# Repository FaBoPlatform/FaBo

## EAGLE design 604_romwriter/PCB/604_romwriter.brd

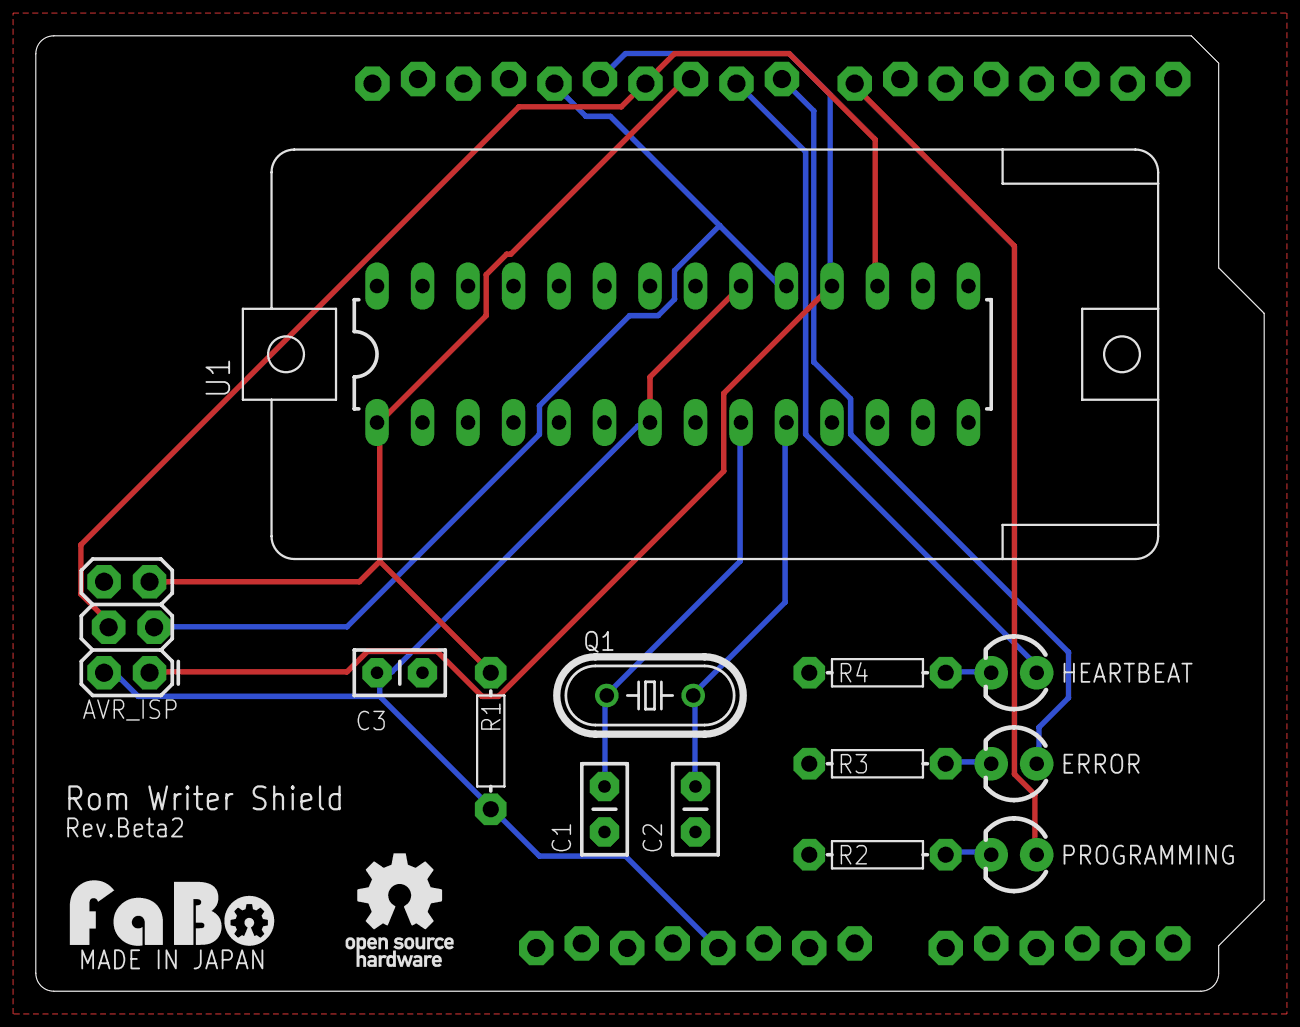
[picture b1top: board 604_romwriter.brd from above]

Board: 2 copper layers, 68.6 x 53.3 mm, 16 parts (0 on the bottom side), 14 nets.

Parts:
C1, C2: 22pF; CAP-PTH-SMALL
C3: 0.01pF; CAP-PTH-SMALL
ERROR: LED3MM
HEARTBEAT: LED3MM
JP1: AVR_ISP; 2X3_LOCK
PROGRAMMING: LED3MM
Q1: HC49/S
R1: 10k; RES-AXL-REGULAR
R2, R3, R4: 1k; RES-AXL-REGULAR
U1: ZERO_PRESSURE_SOCKET; ZERO_PRESSURE_SOCKET_DIL28
U2: ARDUINO_UNO_R3_NOLABEL
U$1: LOGO_FABO_M
U$3: LOGO_OSHW_T_M

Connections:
+5V: C3.1, JP1.2, R1.P$2, U1.7, U1.20, U2.5V
ERR_LED: ERROR.A, U2.D8
GND: C1.2, C2.2, C3.2, JP1.6, R2.P$1, R3.P$1, R4.P$1, U1.8, U1.22, U2.GND1, U2.GND2, U2.GND3
HBT_LED: HEARTBEAT.A, U2.D9
MISO: JP1.1, U1.18, U2.D12
MOSI: JP1.4, U1.17, U2.D11
unnamed: PROGRAMMING.K, R2.P$2
unnamed: ERROR.K, R3.P$2
unnamed: HEARTBEAT.K, R4.P$2
PGM_LED: PROGRAMMING.A, U2.D7
RESET: JP1.5, R1.P$1, U1.1, U2.D10
SCK: JP1.3, U1.19, U2.D13
XTAL1: C1.1, Q1.1, U1.9
XTAL2: C2.1, Q1.2, U1.10

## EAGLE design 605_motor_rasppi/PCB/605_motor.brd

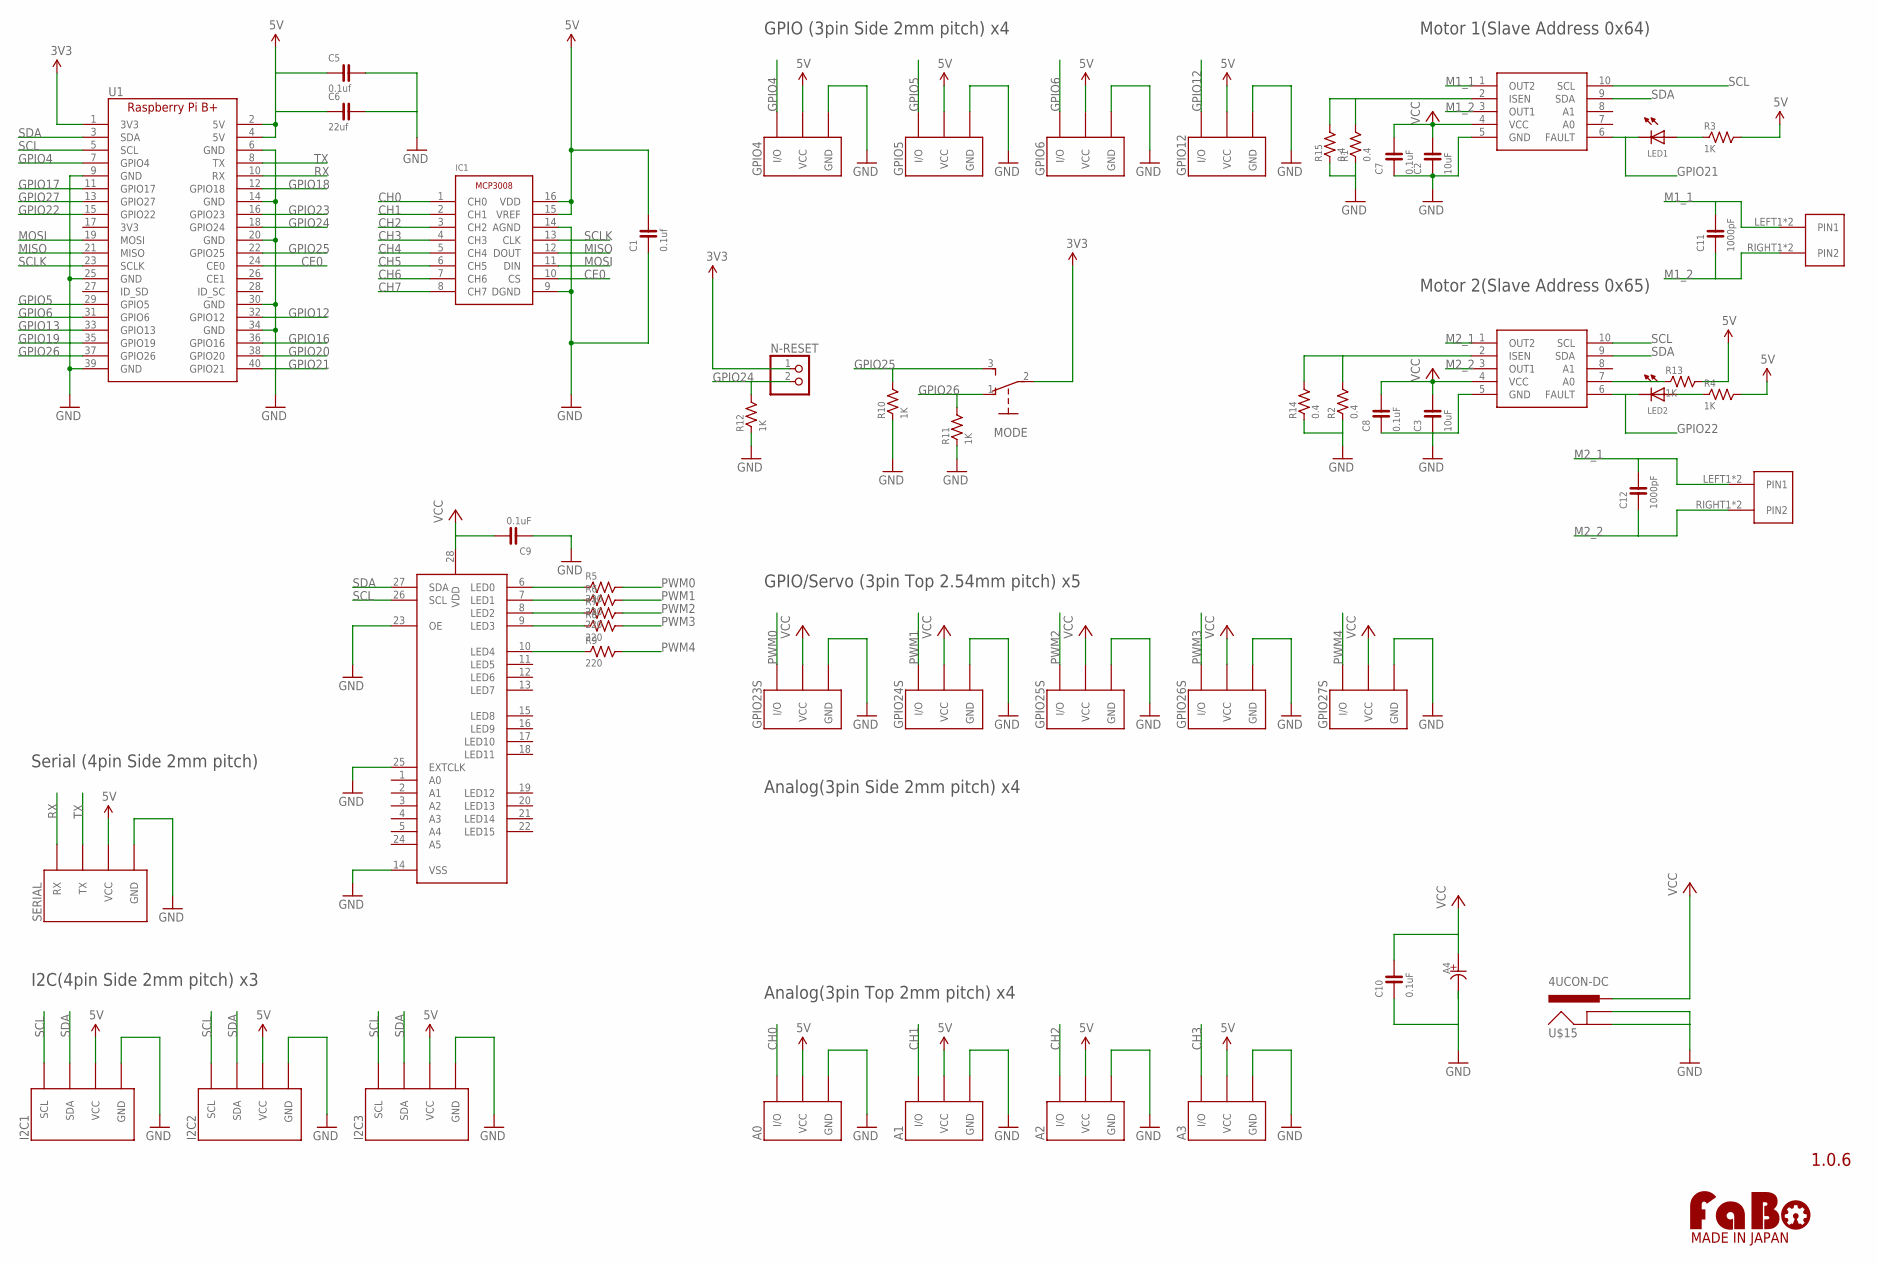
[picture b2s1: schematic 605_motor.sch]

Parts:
A0, A1, A2, A3: FABO_BRICK_3PIN-B03B-PASK-1; FABO_BRICK_3PIN_B03B-PASK-1
A4: CAPACITOR-ALUMIN; H13
C1, C5: 0.1uf; 0603
C2, C3: 10uF; 0603
C6: 22uf; 0603
C7, C8, C9, C10: 0.1uF; 0603
C11, C12: 1000pF; 0603
GPIO4, GPIO5, GPIO6, GPIO12: FABO_BRICK_3PIN-S03B-PASK-2; FABO_BRICK_3PIN_S03B-PASK-2
GPIO23S, GPIO24S, GPIO25S, GPIO26S, GPIO27S: FABO_BRICK_3PIN-HEADER; FABO_BRICK_3PIN_HEADER
I2C1, I2C2, I2C3: FABO_BRICK_I2C-S04B-PASK-2; FABO_BRICK_I2C_S04B-PASK-2
IC1: MICROCHIP-MCP3008
LED1, LED2: LED-0603; 0603
MODE: SLIDE; EG1218
N-RESET: PINHD-1X2; 1X02
R1, R2, R14, R15: 0.4; 0603
R3, R4, R10, R11, R12, R13: 1K; 0603
R5, R6, R7, R8, R9: 220; 0603
SERIAL: FABO_BRICK_SERIAL-S04B-PASK-2; FABO_BRICK_SERIAL_S04B-PASK-2
U1: RASPBERRY_PI_B+
U$8, U$10: DRV8830
U$9: PCA9685
U$12, U$13: ML-1400-S1
U$14: LOGO_FABO-M; LOGO_FABO_MS
U$15: 4UCON-DC

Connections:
3V3: MODE.2, N-RESET.1, U1.1 (3V3)
5V: A0.VCC, A1.VCC, A2.VCC, A3.VCC, C1.2, C5.1, C6.1, GPIO4.VCC, GPIO5.VCC, GPIO6.VCC, GPIO12.VCC, I2C1.VCC, I2C2.VCC, I2C3.VCC, IC1.15 (VREF), IC1.16 (VDD), R3.2, R4.2, R13.2, SERIAL.VCC, U1.2 (5V), U1.4 (5V)
CE0: IC1.10 (CS), U1.24 (CE0)
CH0: A0.I/O, IC1.1 (CH0)
CH1: A1.I/O, IC1.2 (CH1)
CH2: A2.I/O, IC1.3 (CH2)
CH3: A3.I/O, IC1.4 (CH3)
CH4: IC1.5 (CH4)
CH5: IC1.6 (CH5)
CH6: IC1.7 (CH6)
CH7: IC1.8 (CH7)
GND: A0.GND, A1.GND, A2.GND, A3.GND, A4.MINUS (-), C1.1, C2.1, C3.1, C5.2, C6.2, C7.1, C8.1, C9.1, C10.1, GPIO4.GND, GPIO5.GND, GPIO6.GND, GPIO12.GND, GPIO23S.GND, GPIO24S.GND, GPIO25S.GND, GPIO26S.GND, GPIO27S.GND, I2C1.GND, I2C2.GND, I2C3.GND, IC1.9 (DGND), IC1.14 (AGND), R1.1, R2.1, R10.1, R11.1, R12.1, R14.1, R15.1, SERIAL.GND, U1.6 (GND), U1.9 (GND), U1.14 (GND), U1.20 (GND), U1.25 (GND), U1.30 (GND), U1.34 (GND), U1.39 (GND), U$8.5 (GND), U$9.14 (VSS), U$9.23 (OE), U$9.25 (EXTCLK), U$10.5 (GND), U$15.GND1 (GND), U$15.GND2 (GNDBREAK)
GPIO4: GPIO4.I/O, U1.7 (GPIO4)
GPIO5: GPIO5.I/O, U1.29 (GPIO5)
GPIO6: GPIO6.I/O, U1.31 (GPIO6)
GPIO12: GPIO12.I/O, U1.32 (GPIO12)
GPIO13: U1.33 (GPIO13)
GPIO16: U1.36 (GPIO16)
GPIO17: U1.11 (GPIO17)
GPIO18: U1.12 (GPIO18)
GPIO19: U1.35 (GPIO19)
GPIO20: U1.38 (GPIO20)
GPIO21: LED1.CATHODE, U1.40 (GPIO21), U$8.6 (FAULT)
GPIO22: LED2.CATHODE, U1.15 (GPIO22), U$10.6 (FAULT)
GPIO23: U1.16 (GPIO23)
GPIO24: N-RESET.2, R12.2, U1.18 (GPIO24)
GPIO25: MODE.3, R10.2, U1.22 (GPIO25)
GPIO26: MODE.1, R11.2, U1.37 (GPIO26)
GPIO27: U1.13 (GPIO27)
LED0: R5.1, U$9.6 (LED0)
LED1: R6.1, U$9.7 (LED1)
LED2: R7.1, U$9.8 (LED2)
LED3: R8.1, U$9.9 (LED3)
LED4: R9.1, U$9.10 (LED4)
M1_1: C11.2, U$8.1 (OUT2), U$12.LEFT1 (PIN1), U$12.LEFT2 (PIN1)
M1_2: C11.1, U$8.3 (OUT1), U$12.RIGHT1 (PIN2), U$12.RIGHT2 (PIN2)
M2_1: C12.2, U$10.1 (OUT2), U$13.LEFT1 (PIN1), U$13.LEFT2 (PIN1)
M2_2: C12.1, U$10.3 (OUT1), U$13.RIGHT1 (PIN2), U$13.RIGHT2 (PIN2)
MISO: IC1.12 (DOUT), U1.21 (MISO)
MOSI: IC1.11 (DIN), U1.19 (MOSI)
unnamed: R1.2, R15.2, U$8.2 (ISEN)
unnamed: R2.2, R14.2, U$10.2 (ISEN)
unnamed: LED1.ANODE, R3.1
unnamed: R13.1, U$10.7 (A0)
unnamed: LED2.ANODE, R4.1
PWM0: GPIO23S.I/O, R5.2
PWM1: GPIO24S.I/O, R6.2
PWM2: GPIO25S.I/O, R7.2
PWM3: GPIO26S.I/O, R8.2
PWM4: GPIO27S.I/O, R9.2
RX: SERIAL.RX, U1.10 (RX)
SCL: I2C1.SCL, I2C2.SCL, I2C3.SCL, U1.5 (SCL), U$8.10 (SCL), U$9.26 (SCL), U$10.10 (SCL)
SCLK: IC1.13 (CLK), U1.23 (SCLK)
SDA: I2C1.SDA, I2C2.SDA, I2C3.SDA, U1.3 (SDA), U$8.9 (SDA), U$9.27 (SDA), U$10.9 (SDA)
TX: SERIAL.TX, U1.8 (TX)
VCC: A4.PLUS (+), C2.2, C3.2, C7.2, C8.2, C9.2, C10.2, GPIO23S.VCC, GPIO24S.VCC, GPIO25S.VCC, GPIO26S.VCC, GPIO27S.VCC, U$8.4 (VCC), U$9.28 (VDD), U$10.4 (VCC), U$15.VCC (PWR)

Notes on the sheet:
1.0.6
GPIO (3pin Side 2mm pitch) x4
I2C(4pin Side 2mm pitch) x3
Analog(3pin Side 2mm pitch) x4
Serial (4pin Side 2mm pitch)
GPIO/Servo (3pin Top 2.54mm pitch) x5
Analog(3pin Top 2mm pitch) x4
Motor 1(Slave Address 0x64)
Motor 2(Slave Address 0x65)

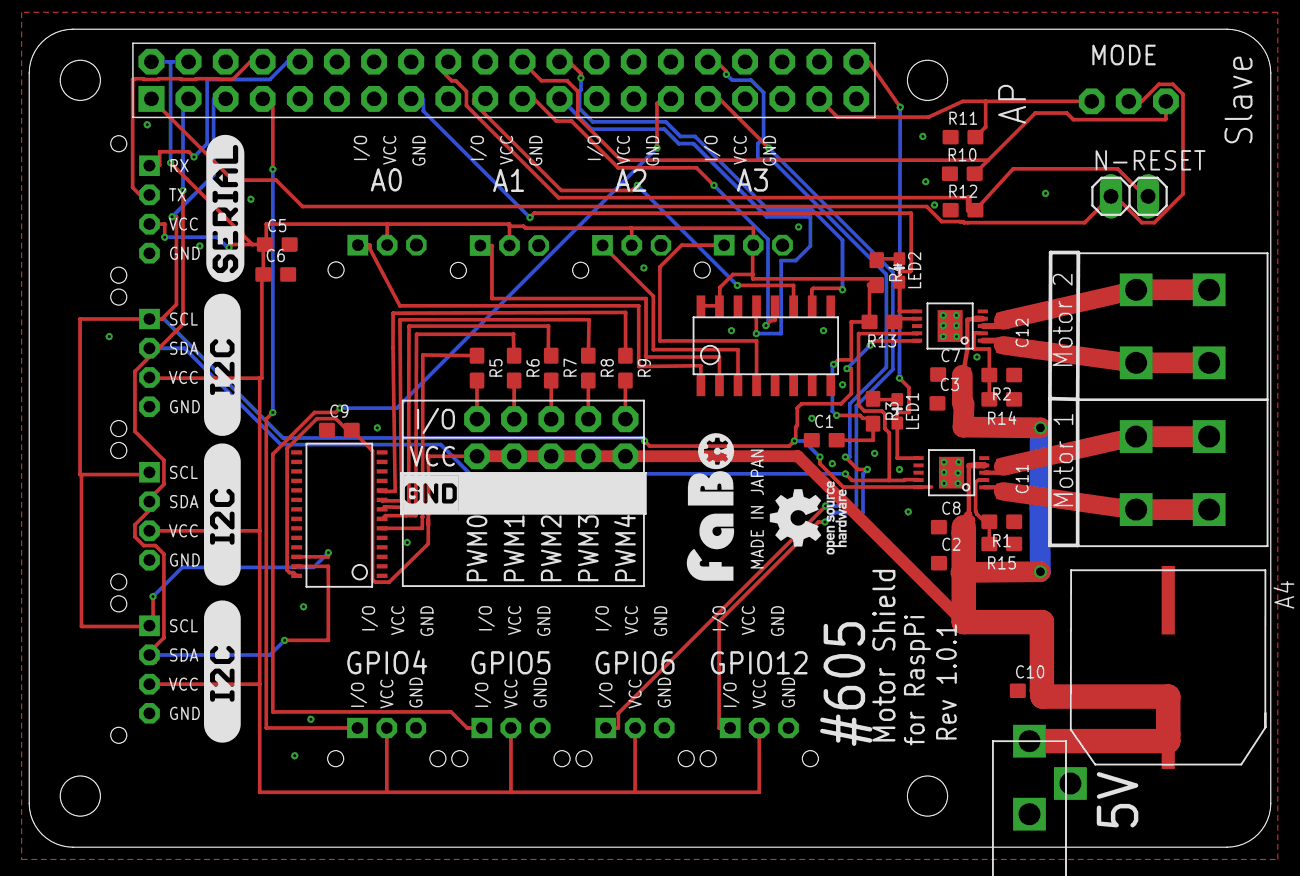
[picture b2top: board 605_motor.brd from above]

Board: 2 copper layers, 85.0 x 56.0 mm, 63 parts (0 on the bottom side), 44 nets.

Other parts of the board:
U$2, U$5, U$6: LOGO_SILK_I2C
U$3: LOGO_SILK_SERIAL2
U$4: LOGO_OSHW_T_MS
U$7: LOGO_SILK_GND

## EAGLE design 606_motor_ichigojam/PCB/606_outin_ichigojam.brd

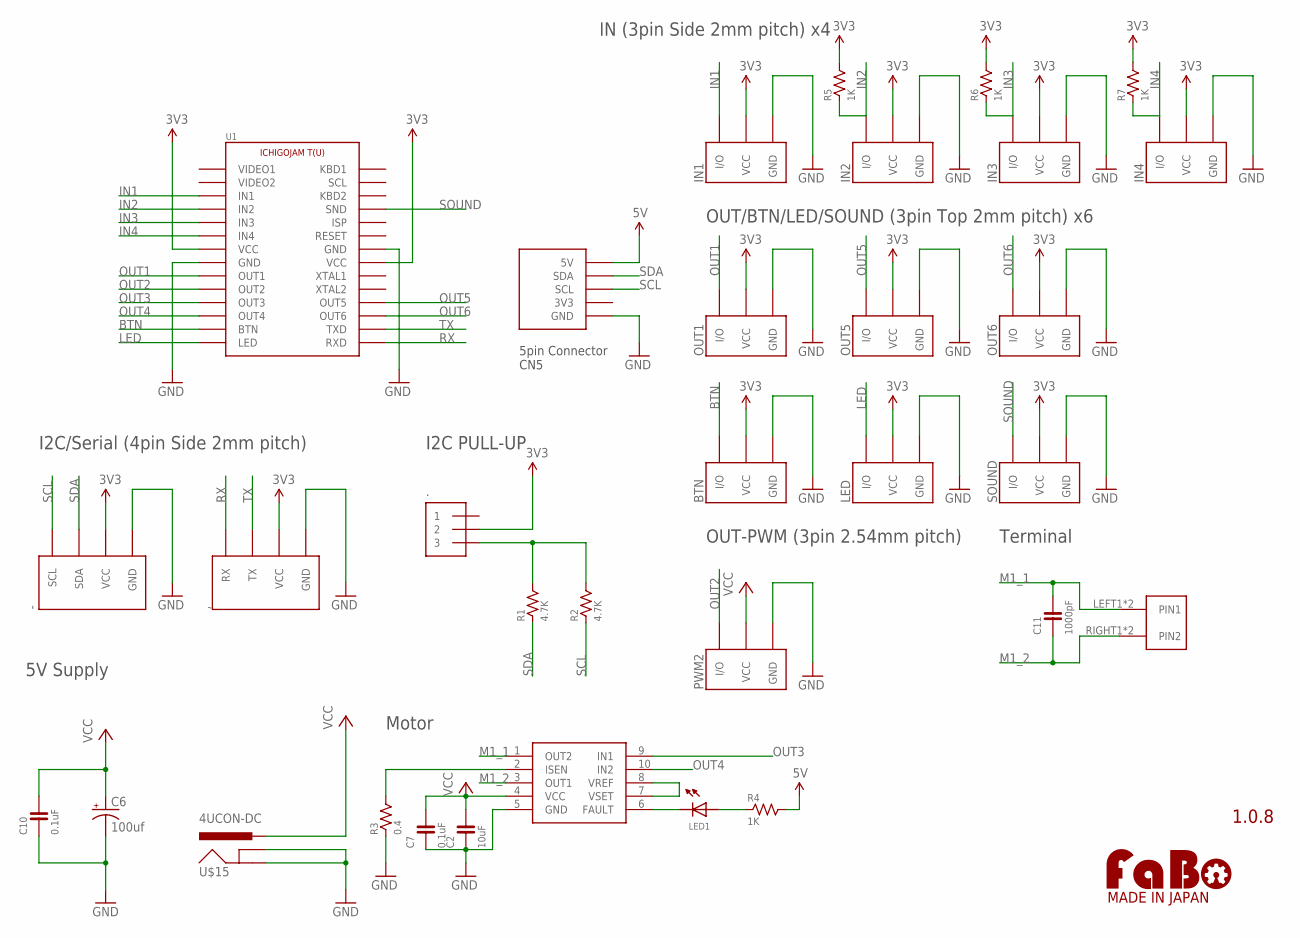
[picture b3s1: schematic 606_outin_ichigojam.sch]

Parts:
,: FABO_BRICK_SERIAL-S04B-PASK-2_LONG; FABO_BRICK_SERIAL_S04B-PASK-2_LONG
-: FABO_BRICK_I2C-S04B-PASK-2_LONG; FABO_BRICK_I2C_S04B-PASK-2_LONG
.: PIN_HEADER_1X3; PIN_1X3
BTN: FABO_BRICK_3PIN-B03B-PASK-1; FABO_BRICK_3PIN_B03B-PASK-1
C2: 10uF; 0603
C6: 100uf; 153CLV-0405
C7, C10: 0.1uF; 0603
C11: 1000pF; 0603
IN1, IN2, IN3, IN4: FABO_BRICK_3PIN-B03B-PASK-1; FABO_BRICK_3PIN_B03B-PASK-1
LED: FABO_BRICK_3PIN-B03B-PASK-1; FABO_BRICK_3PIN_B03B-PASK-1
LED1: LED-0603; 0603
OUT1, OUT5, OUT6: FABO_BRICK_3PIN-B03B-PASK-1; FABO_BRICK_3PIN_B03B-PASK-1
PWM2: FABO_BRICK_3PIN-HEADER; FABO_BRICK_3PIN_HEADER
R1, R2: 4.7K; 0603
R3: 0.4; 0603
R4, R5, R6, R7: 1K; 0603
SOUND: FABO_BRICK_3PIN-B03B-PASK-1; FABO_BRICK_3PIN_B03B-PASK-1
U1: ICHIGOJAM_T-NOLABEL; ICHIGOJAM_T_NOLABEL
U$3: LOGO_FABO-M; LOGO_FABO_MS
U$6: DRV8832; DRV8830
U$12: ML-1400-S1
U$15: 4UCON-DC

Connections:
3V3: ,.VCC, -.VCC, ..2, BTN.VCC, IN1.VCC, IN2.VCC, IN3.VCC, IN4.VCC, LED.VCC, OUT1.VCC, OUT5.VCC, OUT6.VCC, R5.2, R6.2, R7.2, SOUND.VCC, U1.VCC1 (VCC), U1.VCC2 (VCC)
5V: R4.2, U1.5V
BTN: BTN.I/O, U1.BTN
GND: ,.GND, -.GND, BTN.GND, C2.1, C6.-, C7.1, C10.1, IN1.GND, IN2.GND, IN3.GND, IN4.GND, LED.GND, OUT1.GND, OUT5.GND, OUT6.GND, PWM2.GND, R3.1, SOUND.GND, U1.GND1 (GND), U1.GND2 (GND), U1.GND3 (GND), U$6.5 (GND), U$15.GND1 (GND), U$15.GND2 (GNDBREAK)
GPIO21: LED1.CATHODE, U$6.6 (FAULT)
IN1: IN1.I/O, U1.IN1
IN2: IN2.I/O, R5.1, U1.IN2
IN3: IN3.I/O, R6.1, U1.IN3
IN4: IN4.I/O, R7.1, U1.IN4
LED: LED.I/O, U1.LED
M1_1: C11.2, U$6.1 (OUT2), U$12.LEFT1 (PIN1), U$12.LEFT2 (PIN1)
M1_2: C11.1, U$6.3 (OUT1), U$12.RIGHT1 (PIN2), U$12.RIGHT2 (PIN2)
unnamed: ..3, R1.2, R2.2
unnamed: R3.2, U$6.2 (ISEN)
unnamed: U$6.7 (VSET), U$6.8 (VREF)
unnamed: LED1.ANODE, R4.1
OUT1: OUT1.I/O, U1.OUT1
OUT2: PWM2.I/O, U1.OUT2
OUT3: U1.OUT3, U$6.9 (IN1)
OUT4: U1.OUT4, U$6.10 (IN2)
OUT5: OUT5.I/O, U1.OUT5
OUT6: OUT6.I/O, U1.OUT6
RX: ,.RX, U1.RXD
SCL: -.SCL, R2.1, U1.SCL2 (SCL)
SDA: -.SDA, R1.1, U1.SDA
SOUND: SOUND.I/O, U1.SND
TX: ,.TX, U1.TXD
VCC: C2.2, C6.+, C7.2, C10.2, PWM2.VCC, U$6.4 (VCC), U$15.VCC (PWR)

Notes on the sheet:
1.0.8
IN (3pin Side 2mm pitch) x4
OUT/BTN/LED/SOUND (3pin Top 2mm pitch) x6
I2C/Serial (4pin Side 2mm pitch)
I2C PULL-UP
5pin Connector CN5
OUT-PWM (3pin 2.54mm pitch)
5V Supply
Motor
Terminal

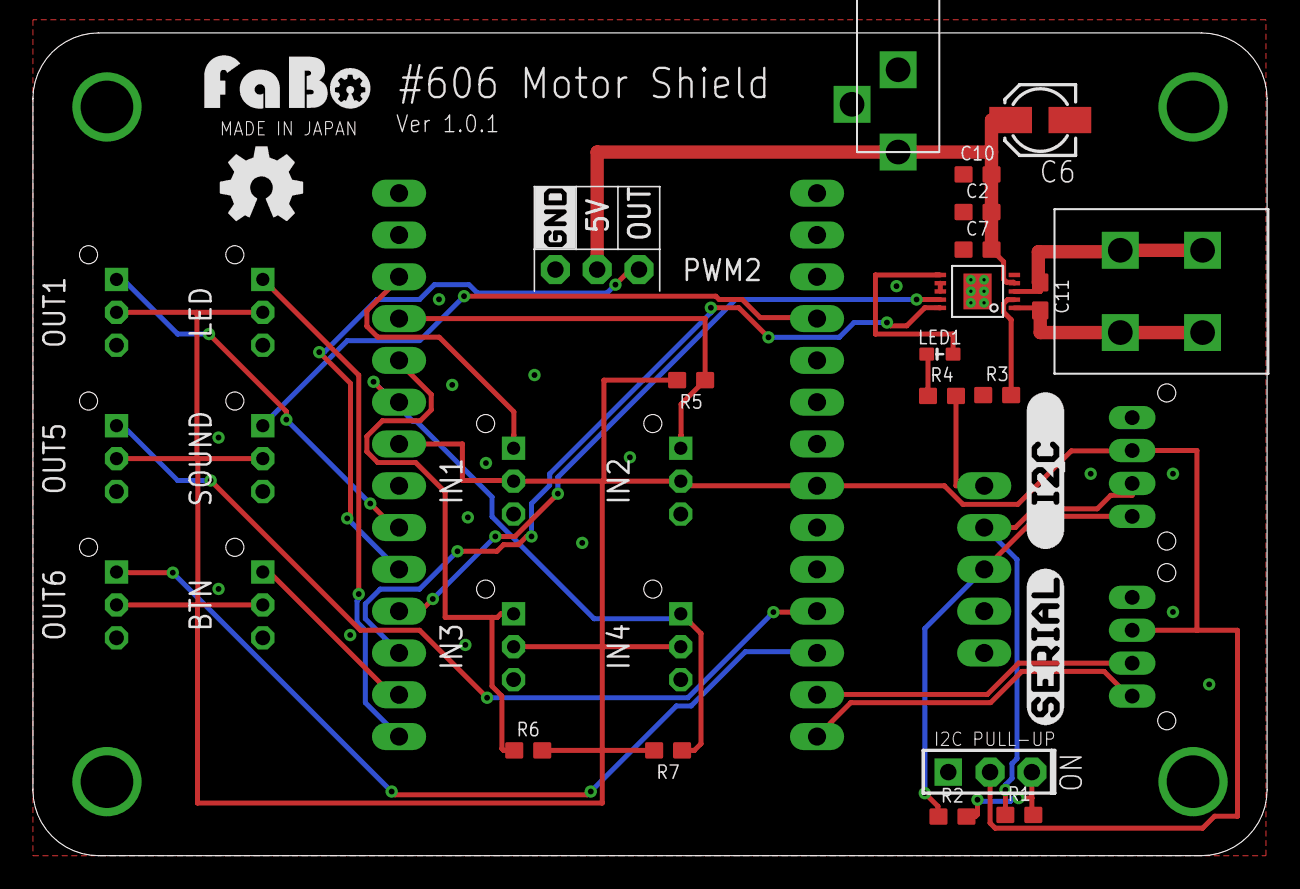
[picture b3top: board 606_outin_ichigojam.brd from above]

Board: 2 copper layers, 75.0 x 50.0 mm, 36 parts (0 on the bottom side), 28 nets.

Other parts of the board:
U$2: LOGO_OSHW_M
U$4: LOGO_SILK_SERIAL2
U$5: LOGO_SILK_I2C
U$7: LOGO_SILK_GND

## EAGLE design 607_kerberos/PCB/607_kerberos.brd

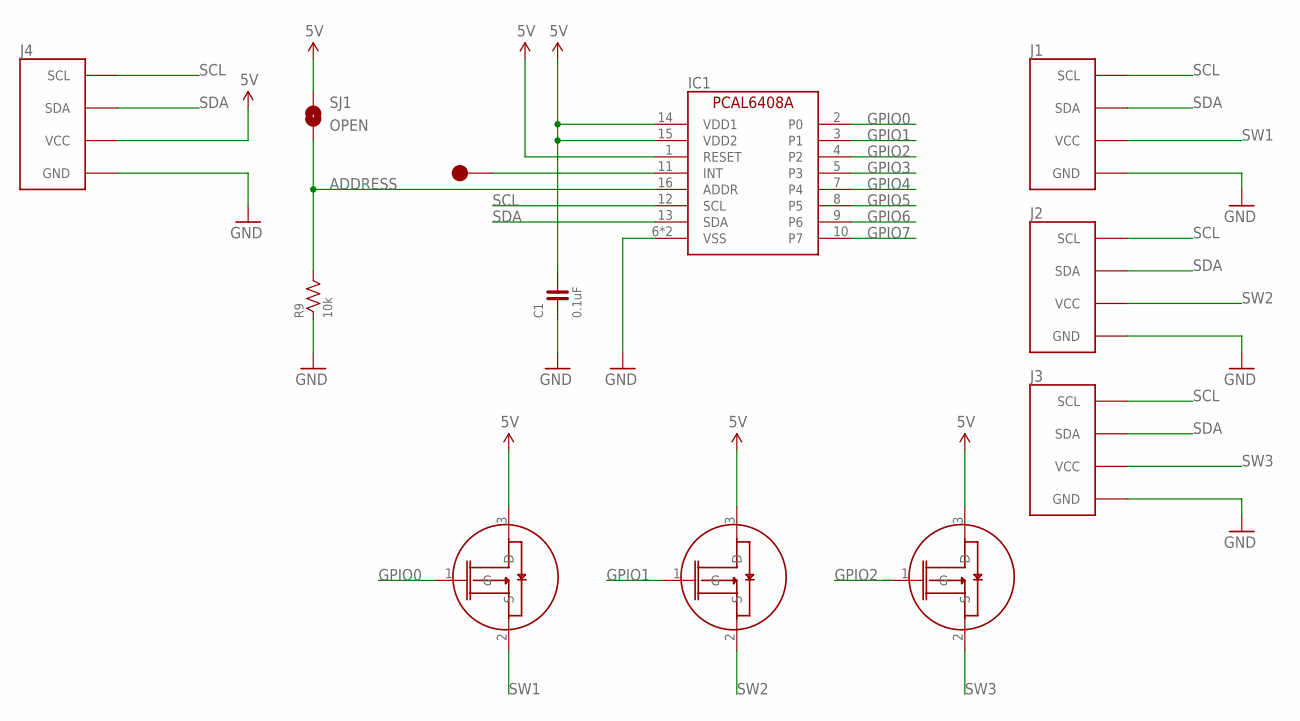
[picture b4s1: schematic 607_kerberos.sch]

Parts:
C1: 0.1uF; 0603
IC1: NX-PCAL6408A; NXP-PCAL6408A
J1, J2, J3, J4: FABO_BRICK_I2C-CONNECTOR; FABO_BRICK_I2C_CONNECTOR
R9: 10k; 0603-NARROW
SJ1: OPEN; SMD-JUMPER-2-OPEN
SW1, SW2, SW3: FAIRCHILD-FDN338; SOT23
TP1: TP-15

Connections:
5V: C1.2, IC1.1 (RESET), IC1.14 (VDD1), IC1.15 (VDD2), J4.VCC, SJ1.1, SW1.3 (D), SW2.3 (D), SW3.3 (D)
ADDRESS: IC1.16 (ADDR), R9.2, SJ1.2
GND: C1.1, IC1.6 (VSS), IC1.17 (VSS), J1.GND, J3.GND, J4.GND, R9.1
GPIO0: IC1.2 (P0), SW1.1 (G)
GPIO1: IC1.3 (P1), SW2.1 (G)
GPIO2: IC1.4 (P2), SW3.1 (G)
GPIO3: IC1.5 (P3)
GPIO4: IC1.7 (P4)
GPIO5: IC1.8 (P5)
GPIO6: IC1.9 (P6)
GPIO7: IC1.10 (P7)
INT: IC1.11 (INT), TP1.1
SCL: IC1.12 (SCL), J1.SCL, J2.SCL, J3.SCL, J4.SCL
SDA: IC1.13 (SDA), J1.SDA, J2.SDA, J3.SDA, J4.SDA
SW1: J1.VCC, SW1.2 (S)
SW2: J2.VCC, SW2.2 (S)
SW3: J3.VCC, SW3.2 (S)

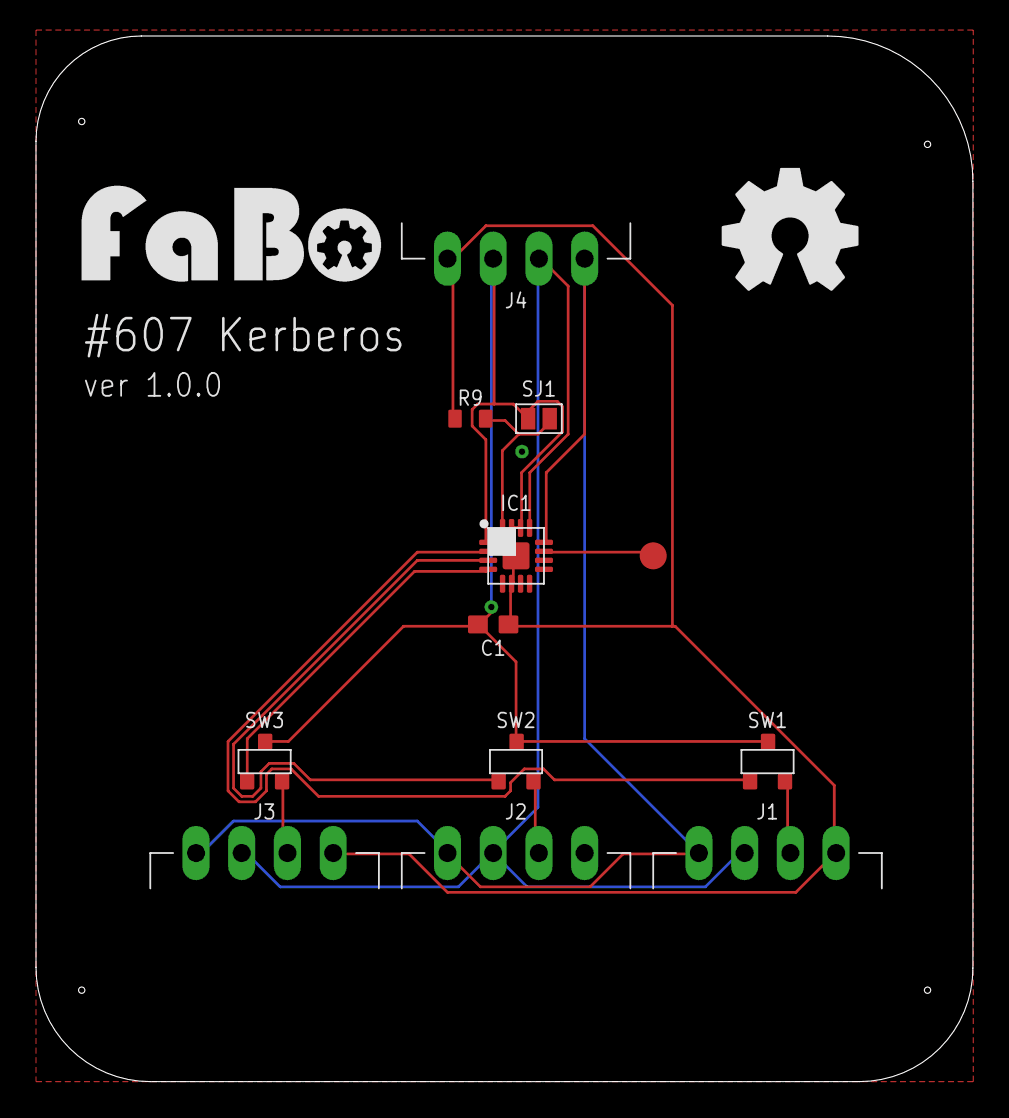
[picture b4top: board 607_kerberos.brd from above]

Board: 2 copper layers, 52.0 x 58.1 mm, 14 parts (0 on the bottom side), 12 nets.

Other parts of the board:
U$2: LOGO_FABO_L
U$3: LOGO_OSHW_L

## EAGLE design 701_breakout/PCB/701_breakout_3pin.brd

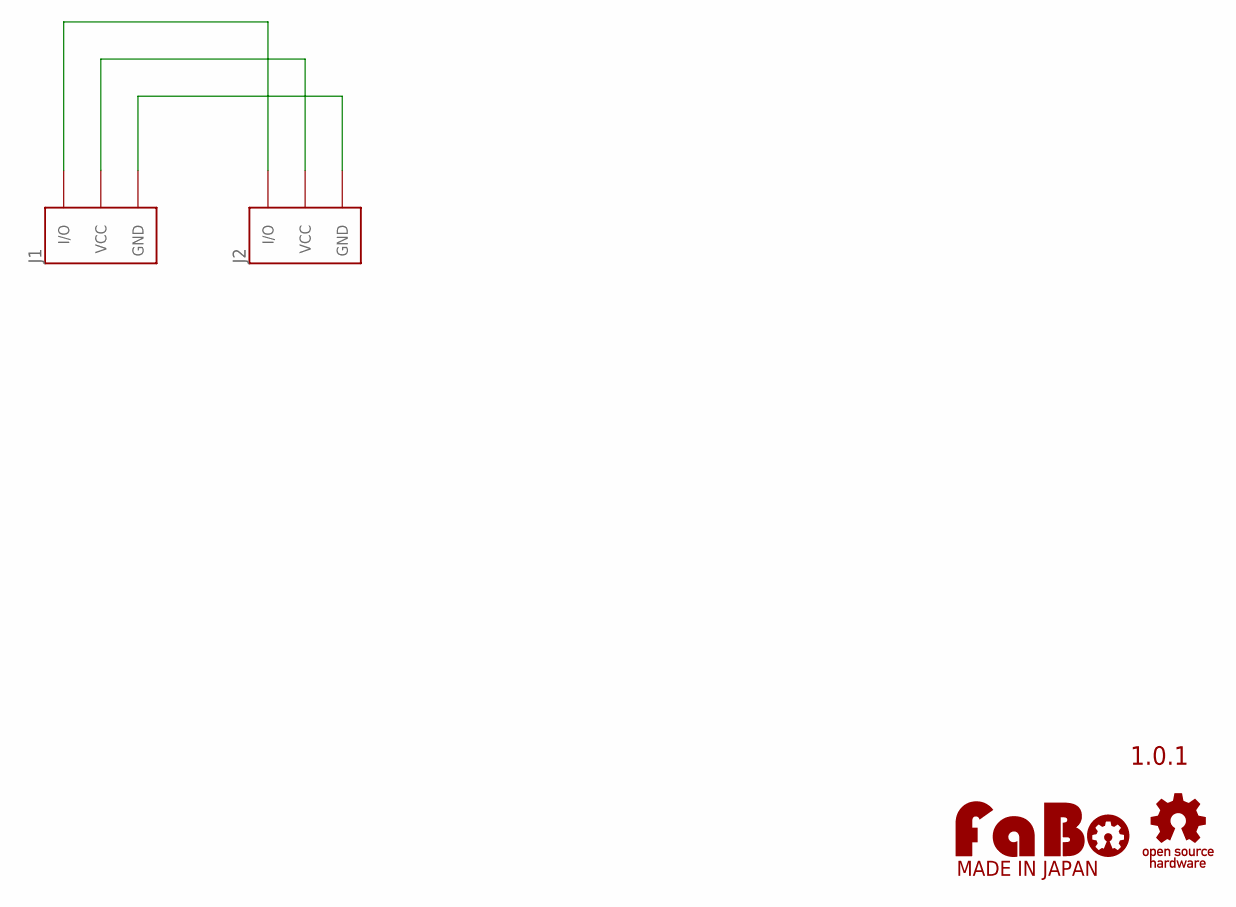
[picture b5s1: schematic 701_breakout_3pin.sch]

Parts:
J1: FABO_BRICK_3PIN-BREAKOUT; FABO_BRICK_3PIN_BREAKOUT
J2: FABO_BRICK_3PIN-CONNECTOR; FABO_BRICK_3PIN_CONNECTOR
U$2: LOGO_FABO-M_BOTTOM; LOGO_FABO_MS_BOTTOM
U$3: LOGO_OSHW-S_BOTTOM; LOGO_OSHW_S_BOTTOM

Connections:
GND: J1.GND, J2.GND
IO: J1.IN/OUT (I/O), J2.IN/OUT (I/O)
VCC: J1.VCC, J2.VCC

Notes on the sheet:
1.0.1

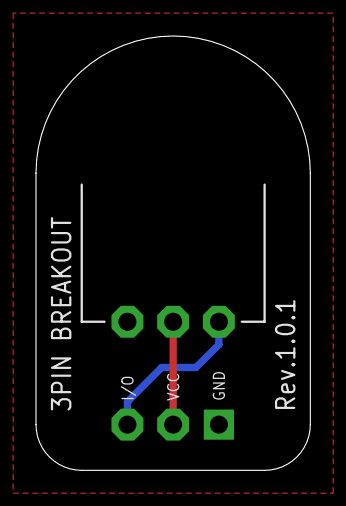
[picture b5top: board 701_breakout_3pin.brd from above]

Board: 2 copper layers, 15.2 x 24.1 mm, 4 parts (0 on the bottom side), 3 nets.

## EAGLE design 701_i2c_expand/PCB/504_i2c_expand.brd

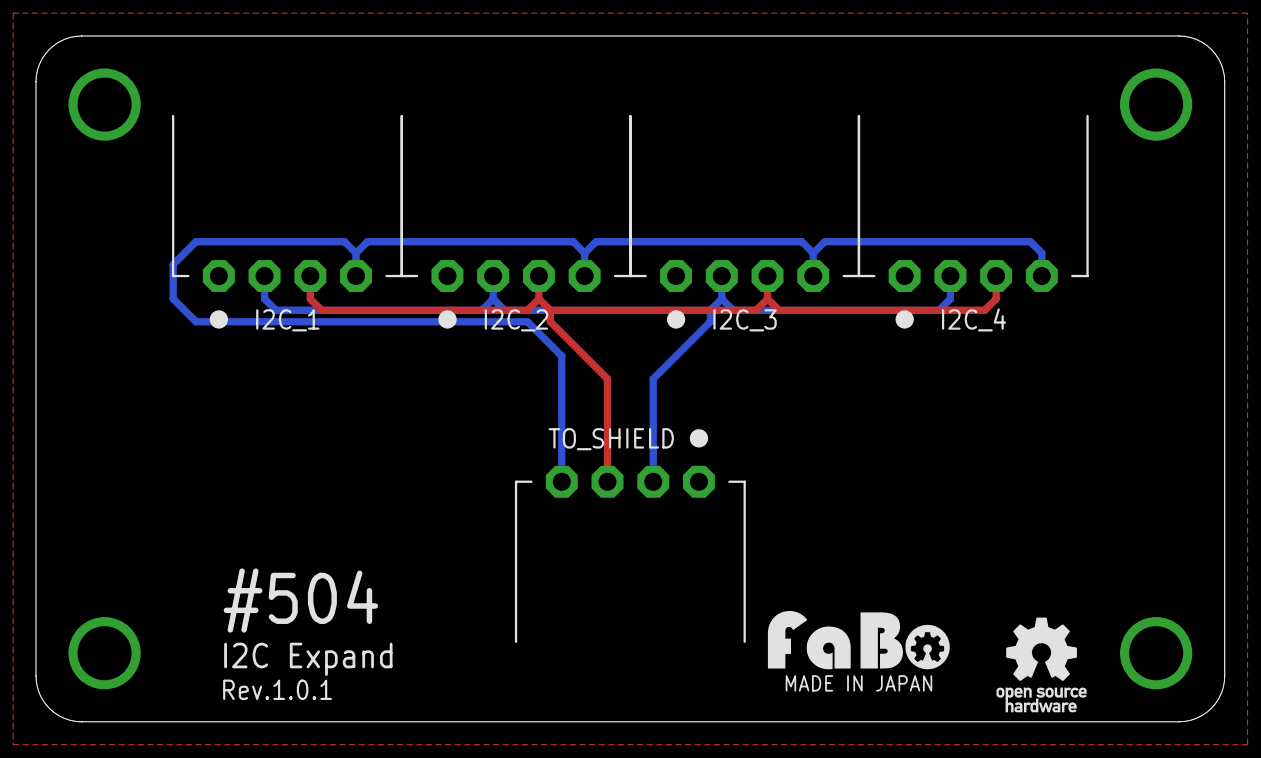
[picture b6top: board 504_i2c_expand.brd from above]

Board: 2 copper layers, 66.0 x 38.1 mm, 11 parts (0 on the bottom side), 4 nets.

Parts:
I2C_1, I2C_2, I2C_3, I2C_4: FABO_BRICK_I2C_CONNECTOR
TO_SHIELD: FABO_BRICK_I2C_CONNECTOR
U$7, U$8, U$9, U$10: SCREWPAD_3MM
U$11: LOGO_OSHW_T_MS
U$12: LOGO_FABO_MS

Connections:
GND: I2C_1.GND, I2C_2.GND, I2C_3.GND, I2C_4.GND, TO_SHIELD.GND
SCL: I2C_1.SCL, I2C_2.SCL, I2C_3.SCL, I2C_4.SCL, TO_SHIELD.SCL
SDA: I2C_1.SDA, I2C_2.SDA, I2C_3.SDA, I2C_4.SDA, TO_SHIELD.SDA
VCC: I2C_1.VCC, I2C_2.VCC, I2C_3.VCC, I2C_4.VCC, TO_SHIELD.VCC

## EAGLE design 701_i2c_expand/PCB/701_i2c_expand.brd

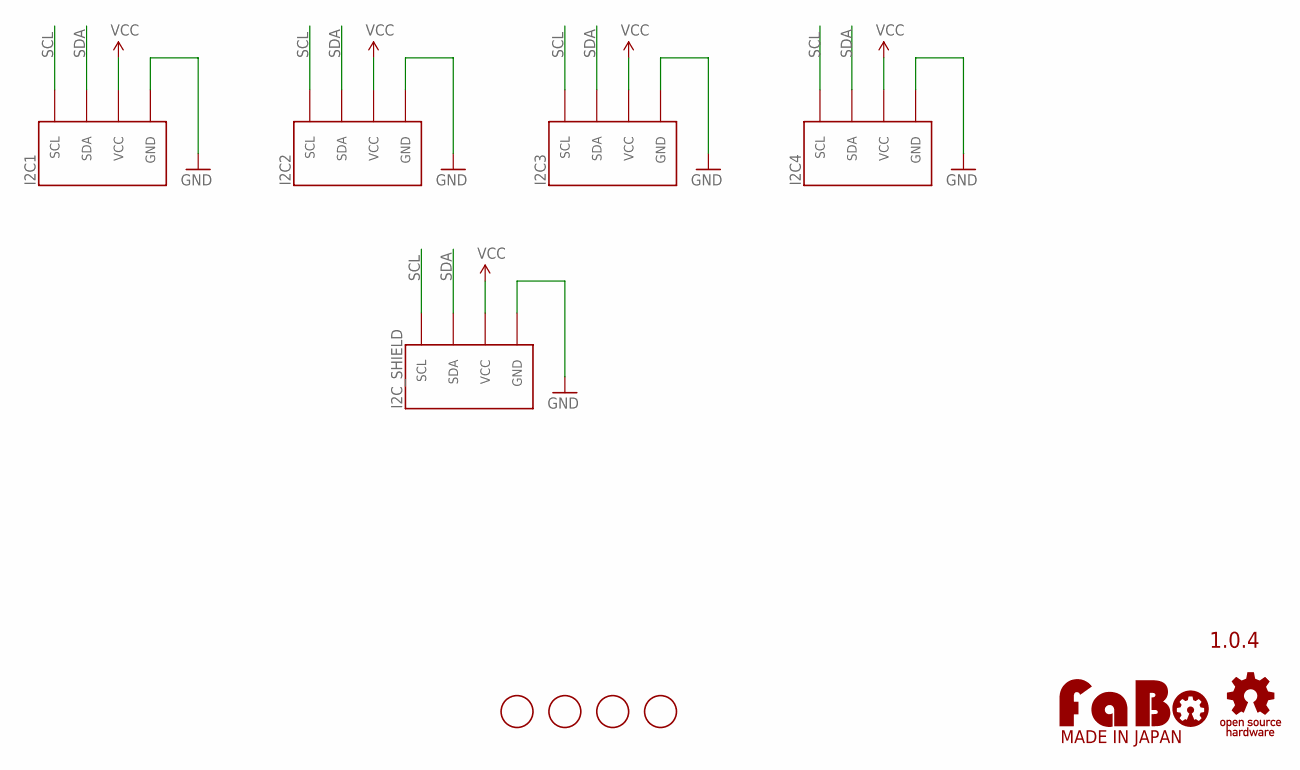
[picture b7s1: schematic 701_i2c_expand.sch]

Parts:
I2C1, I2C2, I2C3, I2C4, I2C_SHIELD: FABO_BRICK_I2C-S04B-PASK-2_LONG; FABO_BRICK_I2C_S04B-PASK-2_LONG
U$7, U$8, U$9, U$10: SCREW-PAD-3MM; SCREWPAD_3MM
U$11: LOGO_OSHW-M_BOTTOM; LOGO_OSHW_M_BOTTOM
U$12: LOGO_FABO-M; LOGO_FABO_MS

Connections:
GND: I2C1.GND, I2C2.GND, I2C3.GND, I2C4.GND, I2C_SHIELD.GND
SCL: I2C1.SCL, I2C2.SCL, I2C3.SCL, I2C4.SCL, I2C_SHIELD.SCL
SDA: I2C1.SDA, I2C2.SDA, I2C3.SDA, I2C4.SDA, I2C_SHIELD.SDA
VCC: I2C1.VCC, I2C2.VCC, I2C3.VCC, I2C4.VCC, I2C_SHIELD.VCC

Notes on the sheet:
1.0.4

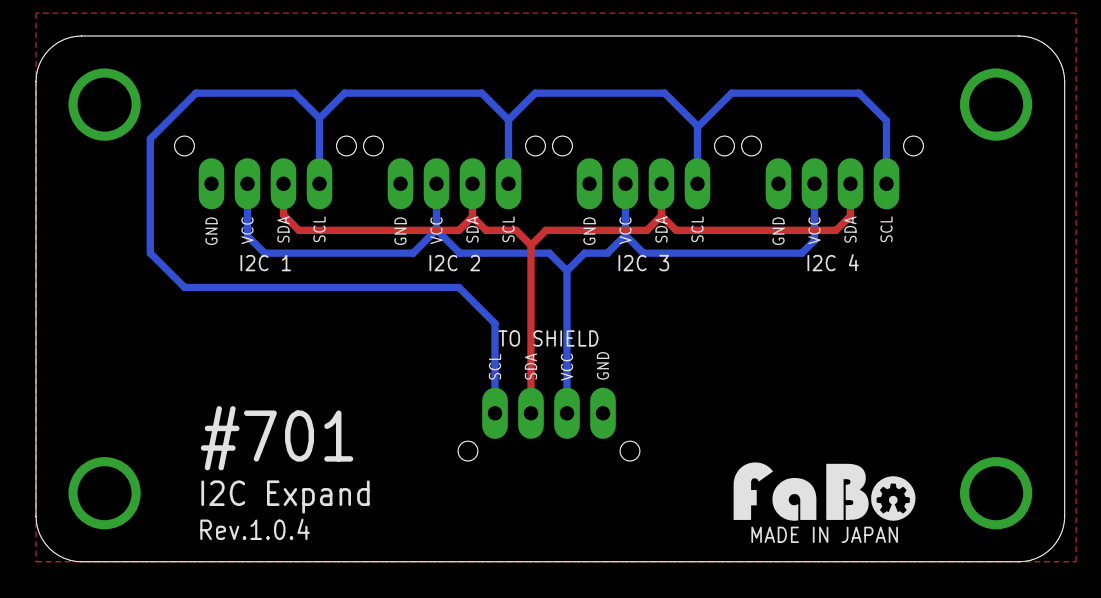
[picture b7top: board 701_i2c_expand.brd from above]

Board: 2 copper layers, 57.1 x 29.2 mm, 11 parts (0 on the bottom side), 4 nets.

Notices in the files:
parts and their libraries:
SparkFun-LED: Licensing: Creative Commons ShareAlike 4.0 International - https://creativecommons.org/licenses/by-sa/4.0
FaBo-etc: Released under the Creative Commons Attribution-ShareAlike 4.0 License
https://creativecommons.org/licenses/by-sa/4.0
FaBo-etc: Released under the Creative Commons
